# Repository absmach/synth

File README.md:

<div align="center">

### Design circuit boards as code.

Turn text-based circuit designs into KiCad schematics, PCB layouts, and bills of materials.

[Install](#install) · [Quick Start](#quick-start) · [Features](#features) · [Examples](#examples) · [Documentation](https://absmach.eu/docs/synth/user-guide/quick-start/) · [Contributing](#contributing)

</div>

## Introduction

Synth is an open-source compiler for electronic circuit boards. Describe components, connections, and board constraints in **SynthSpec**, a text-based design language; Synth checks the design and generates KiCad schematics, PCB layouts, and a bill of materials. Your `.synth` files hold the design intent, so you can edit them in your usual editor and review changes in Git. Engineers drive it from the command line, and AI agents drive the same compiler through its **Model Context Protocol (MCP)** server.

```synth
board "env_logger" {
    layers 2
    manufacturer "jlcpcb"

    group "USB-C INPUT / 3V3 LDO" color "#c2410c" {
      component J1: connector "usb_c_receptacle"
      component U1: regulator "ams1117_3v3" value "AMS1117-3.3"
      component C2: capacitor "c_generic_0805" value "22uF"
    }

    connect J1.vbus -> U1.vin
    connect J1.gnd  -> U1.gnd
    connect U1.vin  -> C2.p1
}
```

_An excerpt from the [environmental logger](examples/env_logger/env_logger.synth); the full design adds the MCU, sensor, CC pull-downs, and decoupling that the checks require._

<div align="center">

_An agent designing a two-layer NE555 LED blinker through the MCP server: searching the registry, authoring a missing part, setting placement overrides, and validating the board._

</div>

## Install

### Prebuilt binary

Every [release](https://github.com/absmach/synth/releases) ships a `synth` binary for five platforms, each with a SHA-256 checksum beside it.

| Platform       | Asset                     |
| -------------- | ------------------------- |
| Linux x86-64   | `synth-linux-amd64`       |
| Linux arm64    | `synth-linux-arm64`       |
| macOS arm64    | `synth-darwin-arm64`      |
| macOS x86-64   | `synth-darwin-amd64`      |
| Windows x86-64 | `synth-windows-amd64.exe` |

```bash
base="https://github.com/absmach/synth/releases/latest/download"
asset="synth-linux-amd64"          # pick your platform from the table above

curl -LO "$base/$asset"
curl -LO "$base/$asset.sha256"
sha256sum -c "$asset.sha256"       # macOS: shasum -a 256 -c "$asset.sha256"

sudo install -m 755 "$asset" /usr/local/bin/synth
synth --version
```

Verify the checksum before running the binary. On Windows, check it with `certutil -hashfile synth-windows-amd64.exe SHA256` and compare against the `.sha256` file.

The Linux binaries are built against glibc 2.35, so they run on Debian Bookworm, Ubuntu 22.04, and newer.

> [!NOTE]
> The component registry and example designs ship inside the repository and track `main`, which has moved ahead of the latest release. Pair a prebuilt binary with its own tag (`git checkout v0.1.1`, where the example paths differ from those below), or install from source to follow the Quick Start as written.

### Cargo

Synth is not on crates.io, so install it from Git. Requires Rust 1.100 or newer.

```bash
# Latest release
cargo install --git https://github.com/absmach/synth --tag v0.1.1 --locked synth-cli

# Current main
cargo install --git https://github.com/absmach/synth --locked synth-cli
```

> [!WARNING]
> Do not run `cargo install synth-cli`. The `synth-cli` crate on crates.io is an unrelated project — a WebAssembly-to-ARM compiler — not this one.

### From source

```bash
git clone https://github.com/absmach/synth.git
cd synth
cargo build -p synth-cli --release
./target/release/synth --help
```

The repository pins its toolchain in `rust-toolchain.toml`, so rustup fetches the right version automatically.

## Quick Start

Validate the minimal example and export a KiCad project. The example designs come from a checkout, so clone the repository (or `cd` into it) first:

```bash
synth validate fixtures/designs/hello.synth
synth export-kicad fixtures/designs/hello.synth --out output/hello
```

The minimal example declares an empty two-layer board. Use the [example designs](#examples) to explore circuits with components and connections.

For machine-readable diagnostics:

```bash
synth validate examples/env_logger/env_logger.synth --format json
```

Open exported projects in KiCad. Optional Gerber, drill, and STEP exports require `kicad-cli`; see the [KiCad workflow guide](docs/kicad-workflows.md) for export and review details.

For CI and release gates, `synth check DESIGN.synth --json` is the deterministic gate for validation, DRC and the testbench when one exists. A check that could not run is reported as `unknown` and blocks just as a failure does — see [release checks](docs/release-checks.md).

### Logging

Progress, retries, and degraded-check notices go to stderr as structured log events; stdout carries only the command's own output (JSON, reports, listings), so a pipeline can parse it without stripping prefixes. The default level is info. `-v` raises it to debug, `-vv` to trace, and `-q` shows errors only. `SYNTH_LOG` overrides both when one stage needs more detail:

```bash
synth -v export-kicad board.synth --out output/board
SYNTH_LOG=synth_router=debug,synth=info synth route board.synth
```

### Agent Integration

Start the MCP server over standard input and output:

```bash
synth mcp --stdio
```

Agents can retrieve the SynthSpec language reference, search the registry, validate designs, apply fixes, and invoke compiler stages. See the [MCP guide](crates/synth-mcp/README.md) for transports and tool details. For electrical checks, the [SPICE simulation skill](skills/spice-sim/SKILL.md) covers authoring a testbench, reading `synth sim` results, and reporting coverage.

## How It Works

```mermaid
flowchart LR
    source["SynthSpec source"] --> compiler["Parse & resolve"]
    compiler --> checks["Validate"]
    checks --> layout["Place & route"]
    layout --> export["KiCad project & BOM"]
    checks --> feedback["Diagnostics & fixes"]
    feedback --> source
```

Synth resolves parts from a component registry and lowers the source into a typed board representation. Compiler stages use that shared representation for electrical checks, layout, routing, and export. A local browser viewer displays the schematic and diagnostics as you edit.

## Features

| Area               | Capabilities                                                                                                                                    |
| ------------------ | ----------------------------------------------------------------------------------------------------------------------------------------------- |
| Design language    | SynthSpec parser, typed board IR, components, connections, differential pairs, keepouts, and placement hints                                    |
| Validation         | Electrical-rule checks, design-rule checks, structured diagnostics with source locations and suggested fixes, and SMT-backed quantitative fixes |
| Layout and routing | Deterministic schematic layout, component placement, and multilayer routing, so generated artifacts are reproducible                            |
| KiCad integration  | Project, schematic, PCB, and BOM export; optional fabrication outputs through `kicad-cli`                                                       |
| Component registry | Versioned parts, project and user overlays, search, import, and authoring tools                                                                 |
| Developer tools    | CLI, JSON diagnostics, and an MCP server exposing validation, registry search, placement, routing, and export                                   |

## Examples

| Design                                                                                             | What it demonstrates                                                          |
| -------------------------------------------------------------------------------------------------- | ----------------------------------------------------------------------------- |
| [Hello](fixtures/designs/hello.synth)                                                              | The smallest board declaration                                                |
| [Resistor divider](examples/divider/divider.synth)                                                 | A DC operating-point simulation with `synth sim`                              |
| [RC filter](examples/rc_filter/rc_filter.synth)                                                    | An AC sweep measuring the -3 dB corner with `synth sim`                       |
| [LED current](examples/led/led.synth)                                                              | A branch-current measure checked against a limit with `synth sim`             |
| [Environmental logger](examples/env_logger/env_logger.synth)                                       | USB-C power, a regulator, an MCU, an environmental sensor, and a debug header |
| [Sensor logger](examples/sensor_logger/sensor_logger.synth)                                        | A larger design with dual I²C sensors, SPI flash, and status LEDs             |
| [Placement and differential pairs](examples/placement_and_diff_pair/placement_and_diff_pair.synth) | Placement hints, differential-pair constraints, and keepout regions           |
| [RP2350 development board](examples/rp2350/)                                                       | Clean-netlist FreeRouting, zone refill, and compact outlines                  |

Additional language and validation cases live in [fixtures](fixtures/designs/README.md). Part definitions live in the [component registry](registry/README.md).

_Pre-generated compact RP2350 routed review artifact; open the [KiCad board](examples/rp2350/rp2350_devboard_freerouting_clean.kicad_pcb)
for an interactive review._

## Documentation

- [Release checks](docs/release-checks.md) — the `synth check` gate, tri-state native stages, and export overrides.
- [KiCad workflows](docs/kicad-workflows.md) — exported projects, validation, BOMs, and fabrication outputs.
- [SPICE simulation](docs/spice-sim.md) — `synth sim` testbenches, analyses, measures and ngspice setup.
- [Schematic procedures](docs/schematic-procedures.md) — schematic generation and review.
- [Diagnostic reference](docs/diagnostics/README.md) — diagnostic codes and repair guidance.
- [Diagnostic protocol](docs/protocol-v1.0.md) — the machine-readable diagnostic format.
- [Component registry](registry/README.md) — part definitions and registry structure.
- [MCP server](crates/synth-mcp/README.md) — agent tools and integration.
- [Glossary](GLOSSARY.md) — shared vocabulary for simulation and check stages.

## Contributing

Contributions to the compiler, component registry, examples, and documentation are welcome. Use [issues](https://github.com/absmach/synth/issues) to report bugs or discuss a change, and submit a pull request with a focused description and relevant validation.

Before submitting code, run the workspace checks:

```bash
make verify
```

This checks formatting, compilation, Clippy lints, the workspace tests, and registry tests. Run `make help` to see individual development commands.

## License

Synth is licensed under the [Apache License 2.0](LICENSE).

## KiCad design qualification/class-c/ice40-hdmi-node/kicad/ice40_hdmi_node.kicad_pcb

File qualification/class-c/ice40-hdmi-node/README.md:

# iCE40HX4K HDMI (DVI-style TMDS) node (Class C, case 3)

An iCE40HX4K FPGA in a 144-pin TQFP (0.5 mm pitch) drives an HDMI Type-A receptacle through four TMDS-style pairs with 270 ohm source resistors. The board also has level-shifted DDC lines, a hot-plug-detect divider, a fused +5 V HDMI pin, an SPI boot flash and four status LEDs. It is powered from a 5 V terminal and is 88.2 x 79.0 mm on six copper layers.

This is the Class C case 3 attempt for #330 under #40. The board declares impedance, pair spacing and skew for its TMDS pairs, and the delivered copper is measured against those declarations. Only the skew budget is met; spacing, coupling and impedance are not (see [#447](https://github.com/absmach/synth/issues/447), open). The interface is DVI-style and no HDMI compliance is claimed.

The prompt to reproduce the board is in [`PROMPT.md`](PROMPT.md), written from the finished board. The prompts the agent ran are in the history at `45b6f93d`.

## The board

### Parts

| Group         | Parts                                                                                                                                         |
| ------------- | --------------------------------------------------------------------------------------------------------------------------------------------- |
| Power entry   | `J1` JST B2B-XH-A 2-pin header, 5.0 to 5.25 V in                                                                                              |
| Power entry   | `F1` Bourns MF-MSMF110/16-2 PTC fuse: 1.1 A hold, 2.2 A trip, 16 V                                                                            |
| Power entry   | `D1` Nexperia PTVS6V0S1UR TVS: 6.0 V standoff, 6.67 V minimum breakdown                                                                       |
| Power entry   | `Q3` Vishay SI2301CDS P-MOSFET (20 V) as the reverse-polarity stage; gate to GND through `R40` (10 k); 5.1 V zener `D_GZ` from gate to source |
| Power entry   | `C1`, test point `TP1`                                                                                                                        |
| 3.3 V         | `U1` Diodes AP7361C-33E-13 LDO: 1 A, SOT-223, stable with ceramic capacitors                                                                  |
| 3.3 V         | `C2` to `C5` 10 uF                                                                                                                            |
| 3.3 V         | `R_SURGE` 1 ohm series resistor in front of `U1`; it keeps a `D1` clamp event off the regulator input                                         |
| 1.2 V core    | `U2` Texas Instruments TLV70012DDCR, TSOT-23-5, with `C6` and `C7`                                                                            |
| 1.2 V core    | PLL supplies `VCCPLL0` and `VCCPLL1` fed through ferrite beads `L1` and `L2`, with `C21` and `C22`                                            |
| FPGA          | `U3` Lattice iCE40HX4K-TQ144, 107 user I/O                                                                                                    |
| FPGA          | 100 nF decoupling `C10` to `C20`, `C24`, `C25` to `C27`                                                                                       |
| FPGA          | `X1` SiTime SiT8008 25 MHz oscillator with `C23`                                                                                              |
| Configuration | `U4` Winbond W25Q128JVSIQ, SOIC-8 208 mil, master SPI                                                                                         |
| Configuration | `R30` and `R31` pull up `CDONE` and `CRESET_B`; `R32` and `R33` pull up the flash write-protect and hold pins                                 |
| HDMI          | `J2` Amphenol 10029449-111RLF HDMI Type-A receptacle                                                                                          |
| HDMI          | `R1` to `R8` 270 ohm TMDS source resistors, in one column between the FPGA and the connector                                                  |
| HDMI          | `D3` onsemi SRV05-4 4-line ESD array on the DDC and HPD lines                                                                                 |
| HDMI          | `D8` and `D9` TI TPD4E05U06 4-channel ESD arrays (0.5 pF per channel) on the eight TMDS lines                                                 |
| HDMI          | `F2` Bourns MF-NSMF050-2 PTC fuse (0.5 A hold) on the +5 V pin                                                                                |
| HDMI          | DDC level shifters `Q1` and `Q2` (IRLML6244), `R9` and `R10` (2 k to +5 V), `R11` and `R12` (10 k to 3.3 V)                                   |
| HDMI          | HPD divider `R13` (10 k) and `R14` (20 k)                                                                                                     |
| Indicators    | `D4` and `D5` green, `D6` and `D7` red LEDs with 470 ohm resistors `R20` to `R23`                                                             |
| Indicators    | `D5` is driven through N-FET `Q4` (AO3400A, gate on `CDONE`), so the open-drain `CDONE` net sees only a gate                                  |
| Test points   | `TP1` to `TP7` on the bottom side: +5 V, +3.3 V, +1.2 V, GND, CDONE, CRESET_B, +5 V_HDMI                                                      |
| Mechanical    | Two M2.5 mounting holes, `H1` and `H2`                                                                                                        |

### Layout

| Item                    | Value                                                                                                                                          |
| ----------------------- | ---------------------------------------------------------------------------------------------------------------------------------------------- |
| Outline                 | 88.5 x 82.0 mm; 1.47 mm thick in the STEP model                                                                                                |
| Copper layers           | 6                                                                                                                                              |
| Stackup                 | JLCPCB `JLC06161H-3313`: prepreg 3313 0.0994 mm er 4.1, core 0.55 mm er 4.6, prepreg 2116 0.1088 mm er 4.16; outer copper 35 um, inner 15.2 um |
| Parts in the BOM        | 83 (74 parts plus 2 mounting holes and 7 test points, which are board features)                                                                |
| Parts placed in the CPL | 74                                                                                                                                             |
| Nets                    | 49                                                                                                                                             |
| Track segments          | 887                                                                                                                                            |
| Vias                    | 141, all at 0.46/0.2 mm                                                                                                                        |
| Track length            | 1922.6 mm                                                                                                                                      |
| Zones and planes        | GND zone on each of the six copper layers; two keepout areas on all layers for the mounting screw heads (no tracks, vias or pour)              |
| Fab package             | `fab/gerbers.zip`, `fab/bom.csv`, `fab/cpl.csv`                                                                                                |
| 3D models               | `models/` holds the STEP body of every part the board references and the board model `ice40_hdmi_node.step`. The board file reaches them by the relative path `${KIPRJMOD}/../models/`. Mounting holes and fiducials have no body. A part that KiCad's library has no model for is a simplified box of its envelope. |
| Schematic               | `images/schematic.pdf`: one vector page, because the board fits one sheet, plotted by `kicad-cli sch export pdf`. |

### Checks

| Check                                  | Result                               | Notes                                                                                                                                       |
| -------------------------------------- | ------------------------------------ | ------------------------------------------------------------------------------------------------------------------------------------------- |
| KiCad DRC (10.0.8, --refill-zones)     | 0 errors, 0 unconnected, 0 warnings  | None                                                                                                                                        |
| KiCad ERC (10.0.8)                     | 0 errors, 0 unconnected, 25 warnings | 18 `lib_symbol_issues`, 5 `lib_symbol_mismatch`, 2 `pin_to_pin`; the 2 `pin_to_pin` are on `CBSEL0` and `CBSEL1`, tied to ground on purpose |
| Routing (KiCadRoutingTools `9399bfb2`) | 49 of 49 nets routed                 | Measured on the board file                                                                                                                  |
| Synth build                            | `main` `8f148bc0` plus 3 fixes        | Branches `feat/jlc-advanced-trace-width` (0.09 mm minimum track), #529 (mirrored text) and `fix/stub-net-by-name` (net spelling, island ties); none is merged, so a plain `main` build does not reproduce this export |
| Gerbers                                | Plotted from refilled zones          | Zones were refilled before the package was written                                                                                          |
| Synth DFM (not a gate)                 | 3 danger, 5 warning on copper        | Pad to via gaps of 0.070 mm at `D8.2` and `U3.24`, and 0.095 mm at `U3.4`; JLCPCB lists 0.0889 mm (3.5 mil) as its minimum on 4 and 6 layers, so the two 0.070 mm gaps are below it. Also 82 silkscreen-to-pad and 19 silkscreen-to-hole danger findings, which JLCPCB clips |
| Via in pad                             | Required                             | The source declares `requires via_in_pad`. An export without it leaves `+3V3` open at `U3` pin 131 and does not release (#512).             |

### Design figures

| Area             | Item                 | Value                                                                                                                                                    | Basis                                               |
| ---------------- | -------------------- | -------------------------------------------------------------------------------------------------------------------------------------------------------- | --------------------------------------------------- |
| FPGA             | User I/O             | 107 on the iCE40HX4K-TQ144                                                                                                                               | Lattice DS1040                                      |
| FPGA             | Part model           | `registry/parts/fpga/ice40hx4k_tq144.synth.toml` is built from KiCad's `FPGA_Lattice:ICE40HX4K-TQ144` symbol with the pin functions of DS1040            | Lattice DS1040                                      |
| Signal integrity | Lane pin assignment  | Four adjacent pin pairs on the FPGA's left side (1-2, 3-4, 7-8, 9-10), in the connector's lane order, so no pair crosses another                         | Measured on the board file                          |
| Signal integrity | Leg definition       | Each leg is the FPGA-to-resistor net plus the resistor-to-connector net; gaps are plan-view, centre to centre, regardless of layer                       | Measured on the board file                          |
| Signal integrity | `D0`                 | P 44.7 mm, N 34.3 mm, skew 10.46 mm, vias 5 / 6, gap min / median 0.17 / 1.80 mm                                                                         | Measured on the board file                          |
| Signal integrity | `D1`                 | P 45.3 mm, N 34.7 mm, skew 10.53 mm, vias 5 / 5, gap min / median 0.00 / 2.13 mm                                                                         | Measured on the board file                          |
| Signal integrity | `D2`                 | P 40.1 mm, N 31.8 mm, skew 8.28 mm, vias 4 / 6, gap min / median 0.00 / 1.71 mm                                                                          | Measured on the board file                          |
| Signal integrity | `CK`                 | P 39.5 mm, N 36.2 mm, skew 3.34 mm, vias 3 / 5, gap min / median 0.04 / 1.77 mm                                                                          | Measured on the board file                          |
| Signal integrity | Minimum gaps         | Gaps below the 0.127 mm track width mean the legs cross in plan view on different layers; they are not a copper spacing                                  | Measured on the board file                          |
| Signal integrity | Skew measure         | Sums of track segments; the DRC's own length-matching figures are not used                                                                               | Measured on the board file                          |
| Signal integrity | Skew budget          | 25 mm declared, met on all four lanes                                                                                                                    | Measured on the board file                          |
| Signal integrity | Skew limit           | 0.15 Tbit within a pair; at 25 MHz Tbit is 4.0 ns, so 0.6 ns, about 85 mm at 7.0 ps/mm; the 25 mm budget is 29 % of it                                   | TI SLVA747 (secondary source); calculated           |
| Signal integrity | Inter-pair mismatch  | Mean pair lengths differ by up to 4.06 mm; no inter-pair budget is declared                                                                              | Measured on the board file                          |
| Signal integrity | Impedance estimate   | 54.5 ohm single-ended, 96.7 ohm differential at 0.127 mm width and 0.15 mm gap, outer-layer microstrip only; it does not describe inner-layer runs       | Calculated (closed-form microstrip)                 |
| Signal integrity | Drive levels         | Each line is LVCMOS33 through 270 ohm into the sink's 50 ohm to 3.3 V: 2.78 V to 3.3 V, 0.52 V single-ended; FPGA pin output impedance not included      | Calculated                                          |
| Signal integrity | Edge rate            | 20 to 80 % edges of at least 0.728 ns at the fast corner; TMDS and source classes declare `edge_rate medium`, a 6 mm window for `W-SYNTH-DRC-016` (#445) | Lattice IBIS model `ice40.ibs` rev 2.5              |
| Signal integrity | Return-via distances | `D0` 0.63 to 4.64 mm, `D1` 1.00 to 4.08 mm, `D2` 0.67 to 5.59 mm, `CK` 0.63 to 4.01 mm; all are inside the 6 mm window                                   | Measured on the board file                          |
| Signal integrity | HPD divider          | 5 V x 20 / (10 + 20) = 3.33 V at the FPGA                                                                                                                | Calculated                                          |
| Power            | Input range          | `J1` takes 5.0 to 5.25 V; protection is sized for a 5.5 V maximum; a 4.75 V low-end check shows why 5.0 V is the minimum                                 | Calculated                                          |
| Power            | `D1` standoff        | 6.0 V standoff above the 5.5 V maximum input                                                                                                             | Nexperia PTVS6V0S1UR datasheet                      |
| Power            | HDMI pin 18 drop     | Worst case 0.065 V in `F1`, 0.034 V in `Q3`, 0.039 V in `F2`, 0.138 V in all                                                                             | Calculated                                          |
| Power            | HDMI pin 18 voltage  | A 5.00 V input gives 4.86 V against the 4.8 V minimum; pin 18 needs at least 4.94 V at `J1`                                                              | Calculated                                          |
| Power            | Regulator ratings    | `RthJA` 110 degC/W (SOT-223); 6.0 V recommended, 6.5 V absolute maximum input; 360 mV typical dropout at 1 A                                             | Diodes DS37274 Rev. 5-2                             |
| Power            | Dropout margin       | At the 4.40 V worst-case regulator input, `U1` has 1.10 V to spare against 0.36 V typical dropout at 1 A                                                 | Diodes DS37274 Rev. 5-2; calculated                 |
| Thermal          | 3.3 V load           | `U2` 200 mA, `U4` 25 mA, LEDs 28 mA: 253 mA                                                                                                              | TI SBVS173; Winbond W25Q128JV datasheet; calculated |
| Thermal          | `U1` junction        | 0.47 W in `U1`; Tj 77 degC at 25 degC and 122 degC at 70 degC ambient                                                                                    | Diodes DS37274 Rev. 5-2; calculated                 |
| Protection       | Surge clamp          | `D1` clamps at up to 10.3 V                                                                                                                              | Nexperia PTVS6V0S1UR datasheet                      |
| Protection       | Surge current        | `R_SURGE` limits the current into `C2` and `C3` (20 uF) to 5.8 A; a 60 ns event raises the regulator input by about 0.02 V                               | Calculated                                          |
| Protection       | `Q3` gate            | `D_GZ` holds the `Q3` gate-source voltage under 5.4 V against its 8 V rating                                                                             | Vishay SI2301CDS datasheet; calculated              |
| Assembly         | Via in pad           | The TQFP-144 escape does not need it; the plane stage does until #512 is fixed. A few vias sit in small-part and test-point pads                         | Measured on the board file                          |

### Sourcing

| Item                        | Status                 | Notes                                         |
| --------------------------- | ---------------------- | --------------------------------------------- |
| 74 placed parts             | sourced                | Distributor and order number in `fab/bom.csv` |
| `H1`, `H2`, `TP1` to `TP7`  | board feature, no part | Not placed                                    |
| JLCPCB DFM and BOM matching | not run                | No run is recorded for the package in `fab/`  |

## Not verified by Synth

| Area                   | What is not verified                                                                                                                                                               |
| ---------------------- | ---------------------------------------------------------------------------------------------------------------------------------------------------------------------------------- |
| HDMI compliance        | None is claimed. The interface is DVI-style, with LVCMOS33 outputs through series resistors, because the iCE40 cannot source TMDS levels.                                          |
| Coupled pairs          | The pairs are routed as independent nets on different layers, so they are not a coupled differential interface.                                                                    |
| Impedance              | The differential impedance is not established. Only an analytic estimate for an outer-layer microstrip is given.                                                                   |
| Pair spacing           | The median gap between the legs, 1.71 to 2.13 mm, is wider than the declared 0.15 mm coupling gap, so the legs are not coupled.                                                    |
| Sustained over-voltage | While `D1` holds the rail near 7.0 V until `F1` opens, the regulator input is about 6.75 V, 0.25 V over its 6.5 V rating.                                                          |
| `R_SURGE` pulse rating | The 5.8 A, 60 ns event is not checked against the resistor's pulse-load curve.                                                                                                     |
| Back-drive             | A powered sink back-powers the FPGA banks through the 270 ohm resistors when the board is off. No isolation switch is fitted. Do not connect a powered sink to an unpowered board. |
| FPGA I/O current       | The thermal budget leaves about 0.02 A for the FPGA's 3.3 V I/O at 70 degC ambient. That current depends on the FPGA design and is not counted.                                    |
| Test-point probing     | The effect of filled vias in the `TP2` and `TP5` pads on probing is not assessed.                                                                                                  |
| Fabrication checks     | No JLCPCB DFM or BOM-matching run is recorded for the package in `fab/`.                                                                                                           |
| Independent sign-off   | The independent PCB review required by #40 is still open.                                                                                                                          |

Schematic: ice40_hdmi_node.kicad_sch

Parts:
C1, C2, C3, C4, C5: 10uF; C_0805_2012Metric
C6, C7: 1uF; C_0603_1608Metric
C8: 100nF; C_0603_1608Metric
C10, C11, C12, C13, C14, C15, C16, C17, C18, C19, C20, C21, C22, C23, C24, C25, C26, C27: 100nF; C_0402_1005Metric
D1: PTVS6V0S1UR; Nexperia_CFP3_SOD-123W; MPN PTVS6V0S1UR
D3: SRV05-4MR6T1G; SOT-23-6; MPN SRV05-4MR6T1G
D4, D5: 0603-GREEN; LED_0603_1608Metric; MPN 0603-GREEN; LCSC C72043
D6, D7: 0603-RED; LED_0603_1608Metric; MPN 0603-RED; LCSC C2286
D8, D9: TPD4E05U06DQAR; USON-10_2.5x1.0mm_P0.5mm; MPN TPD4E05U06DQAR; LCSC C138714
D_GZ: 5V1; D_SOD-123; MPN BZT52C5V1-TP; LCSC C78728
F1: MF-MSMF110/16-2; Fuse_1812_4532Metric; MPN MF-MSMF110/16-2; LCSC C210834
F2: MF-NSMF050-2; Fuse_1206_3216Metric; MPN MF-NSMF050-2; LCSC C75464
H1, H2: (no value); MountingHole_2.5mm
J1: B2B-XH-A; JST_XH_B2B-XH-A_1x02_P2.50mm_Vertical; MPN B2B-XH-A
J2: 10029449-111RLF; HDMI_A_Amphenol_10029449-x01xLF_Horizontal; MPN 10029449-111RLF; LCSC C427307
L1, L2: (no value); L_0603_1608Metric
Q1, Q2: IRLML6244TRPBF; SOT-23; MPN IRLML6244TRPBF; LCSC C143946
Q3: SI2301CDS-T1-GE3; SOT-23; MPN SI2301CDS-T1-GE3; LCSC C10487
Q4: AO3400A; SOT-23; MPN AO3400A
R1, R2, R3, R4, R5, R6, R7, R8: 270; R_0603_1608Metric
R9, R10: 2k; R_0603_1608Metric
R11, R12, R13, R30, R31, R32, R33, R40: 10k; R_0603_1608Metric
R14: 20k; R_0603_1608Metric
R20, R21, R22, R23: 470; R_0603_1608Metric
R_SURGE: 1; R_1206_3216Metric
TP1: +5V; TestPoint_Pad_D1.5mm
TP2: +3V3; TestPoint_Pad_D1.5mm
TP3: +1V2; TestPoint_Pad_D1.5mm
TP4: GND; TestPoint_Pad_D1.5mm
TP5: CDONE; TestPoint_Pad_D1.5mm
TP6: CRESET_B; TestPoint_Pad_D1.5mm
TP7: +5V_HDMI; TestPoint_Pad_D1.5mm
U1: AP7361C-33E; SOT-223-3_TabPin2; MPN AP7361C-33E-13; LCSC C500795
U2: TLV70012DDCR; TSOT-23-5; MPN TLV70012DDCR; LCSC C69446
U3: ICE40HX4K-TQ144; TQFP-144_20x20mm_P0.5mm; MPN ICE40HX4K-TQ144; LCSC C1521989
U4: W25Q128JVSIQ; SOIC-8_5.3x5.3mm_P1.27mm; MPN W25Q128JVSIQ; LCSC C97521
X1: 25MHz; Oscillator_SMD_SiT_PQFN-4Pin_5.0x3.2mm

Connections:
+1V2: C7.1, C10.1, C11.1, C12.1, C13.1, L1.1, L2.1, TP3.1, U2.5 (OUT), U3.27 (VCC), U3.40 (VCC), U3.92 (VCC), U3.111 (VCC)
+1V2_PLL0: C21.1, L1.2, U3.54 (VCCPLL0)
+1V2_PLL1: C22.1, L2.2, U3.126 (VCCPLL1)
+3V3: C4.1, C5.1, C6.1, C14.1, C15.1, C16.1, C17.1, C18.1, C19.1, C20.1, C23.1, C24.1, C25.1, C26.1, C27.1, Q1.1 (G), Q2.1 (G), R11.1, R12.1, R20.1, R21.1, R30.1, R31.1, R32.1, R33.1, TP2.1, U1.3 (VO), U2.1 (IN), U2.3 (EN), U3.6 (VCCIO_3), U3.30 (VCCIO_3), U3.46 (VCCIO_2), U3.57 (VCCIO_2), U3.72 (VCC_SPI), U3.89 (VCCIO_1), U3.100 (VCCIO_1), U3.108 (VPP_2V5), U3.109 (VPP_FAST), U3.123 (VCCIO_0), U3.131 (VCCIO_0), U4.8 (VCC), X1.1 (OE), X1.4 (Vdd)
+5V: C1.1, D_GZ.1 (K), F2.1, Q3.2 (s), R_SURGE.1, TP1.1
+5V_HDMI: C8.1, D3.5 (VP), F2.2, J2.18 (+5V), R9.1, R10.1, TP7.1
+5V_IN: F1.1, J1.1
+5V_REG: C2.1, C3.1, R_SURGE.2, U1.1 (VI)
CDONE: Q4.1 (G), R30.2, TP5.1, U3.65 (CDONE)
CK_N_SRC: R8.1, U3.1 (IOL_2A)
CK_P_SRC: R7.1, U3.2 (IOL_2B)
CLK25: U3.128 (IOT_197_GBIN1), X1.3 (OUT)
CRESET_B: R31.2, TP6.1, U3.66 (~CRESET)
D0_N_SRC: R2.1, U3.3 (IOL_3A)
D0_P_SRC: R1.1, U3.4 (IOL_3B)
D1_N_SRC: R4.1, U3.7 (IOL_4A)
D1_P_SRC: R3.1, U3.8 (IOL_4B)
D2_N_SRC: R6.1, U3.9 (IOL_5A)
D2_P_SRC: R5.1, U3.10 (IOL_5B)
FLASH_HOLD: R33.2, U4.7 (~HOLD/~RESET/IO_{3})
FLASH_WP: R32.2, U4.3 (~WP/IO_{2})
GND: C1.2, C2.2, C3.2, C4.2, C5.2, C6.2, C7.2, C8.2, C10.2, C11.2, C12.2, C13.2, C14.2, C15.2, C16.2, C17.2, C18.2, C19.2, C20.2, C21.2, C22.2, C23.2, C24.2, C25.2, C26.2, C27.2, D1.2 (A), D3.2 (VN), D4.1 (K), D6.1 (K), D7.1 (K), D8.3 (GND), D8.8 (GND), D9.3 (GND), D9.8 (GND), J1.2, J2.2 (D2S), J2.5 (D1S), J2.8 (D0S), J2.11 (CKS), J2.17 (GND), J2.SH, Q4.2 (S), R14.2, TP4.1, U1.2 (GND), U2.2 (GND), U3.5 (GND), U3.13 (GND), U3.14 (GND), U3.53 (GNDPLL0), U3.59 (GND), U3.63 (IOB_103_CBSEL0), U3.64 (IOB_104_CBSEL1), U3.69 (GND), U3.86 (GND), U3.103 (GND), U3.127 (GNDPLL1), U3.132 (GND), U3.140 (GND), U4.4 (GND), X1.2 (GND)
HDMI_CK_N: D9.5 (D2-), J2.12 (CK-), R8.2
HDMI_CK_P: D9.4 (D2+), J2.10 (CK+), R7.2
HDMI_D0_N: D8.2 (D1-), J2.9 (D0-), R2.2
HDMI_D0_P: D8.1 (D1+), J2.7 (D0+), R1.2
HDMI_D1_N: D8.5 (D2-), J2.6 (D1-), R4.2
HDMI_D1_P: D8.4 (D2+), J2.4 (D1+), R3.2
HDMI_D2_N: D9.2 (D1-), J2.3 (D2-), R6.2
HDMI_D2_P: D9.1 (D1+), J2.1 (D2+), R5.2
HDMI_HPD: D3.4 (IO3), J2.19 (HPD/HEAC-), R13.1
HDMI_SCL: D3.3 (IO2), J2.15 (SCL), Q2.3 (D), R10.2
HDMI_SDA: D3.1 (IO1), J2.16 (SDA), Q1.3 (D), R9.2
HPD_FPGA: R13.2, R14.1, U3.19 (IOL_13A)
LED1_A: D6.2 (A), R22.2
LED2_A: D7.2 (A), R23.2
LED_DONE: D5.2 (A), R21.2
LED_DONE_K: D5.1 (K), Q4.3 (D)
LED_PWR: D4.2 (A), R20.2
LED_USER1: R22.1, U3.37 (IOB_56)
LED_USER2: R23.1, U3.39 (IOB_61)
Q3_GATE: D_GZ.2 (A), Q3.1 (g), R40.1
SCL_FPGA: Q2.2 (S), R12.2, U3.24 (IOL_17B)
SDA_FPGA: Q1.2 (S), R11.2, U3.23 (IOL_17A)
SPI_MISO: U3.68 (IOB_106_SDI), U4.2 (DO/IO_{1})
SPI_MOSI: U3.67 (IOB_105_SDO), U4.5 (DI/IO_{0})
SPI_SCK: U3.70 (IOB_107_SCK), U4.6 (CLK)
SPI_SS: U3.71 (IOB_108_SS), U4.1 (~CS)
VIN_FUSED: D1.1 (K), F1.2, Q3.3 (d)

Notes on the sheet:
POWER ENTRY
RAILS
FPGA
CONFIG FLASH
HDMI
STATUS
5 V in; PTC 1.1 A hold; TVS 6.0 V standoff above the 5.5 V maximum input; Q3 P-MOSFET reverse-polarity stage, gate to GND through R40.
TMDS drive: FPGA LVCMOS33 output + 270 ohm into 50 ohm sink pull-up to 3.3 V.
D8 and D9 are TPD4E05U06 ESD arrays (0.5 pF per channel) on the eight TMDS lines at the connector.

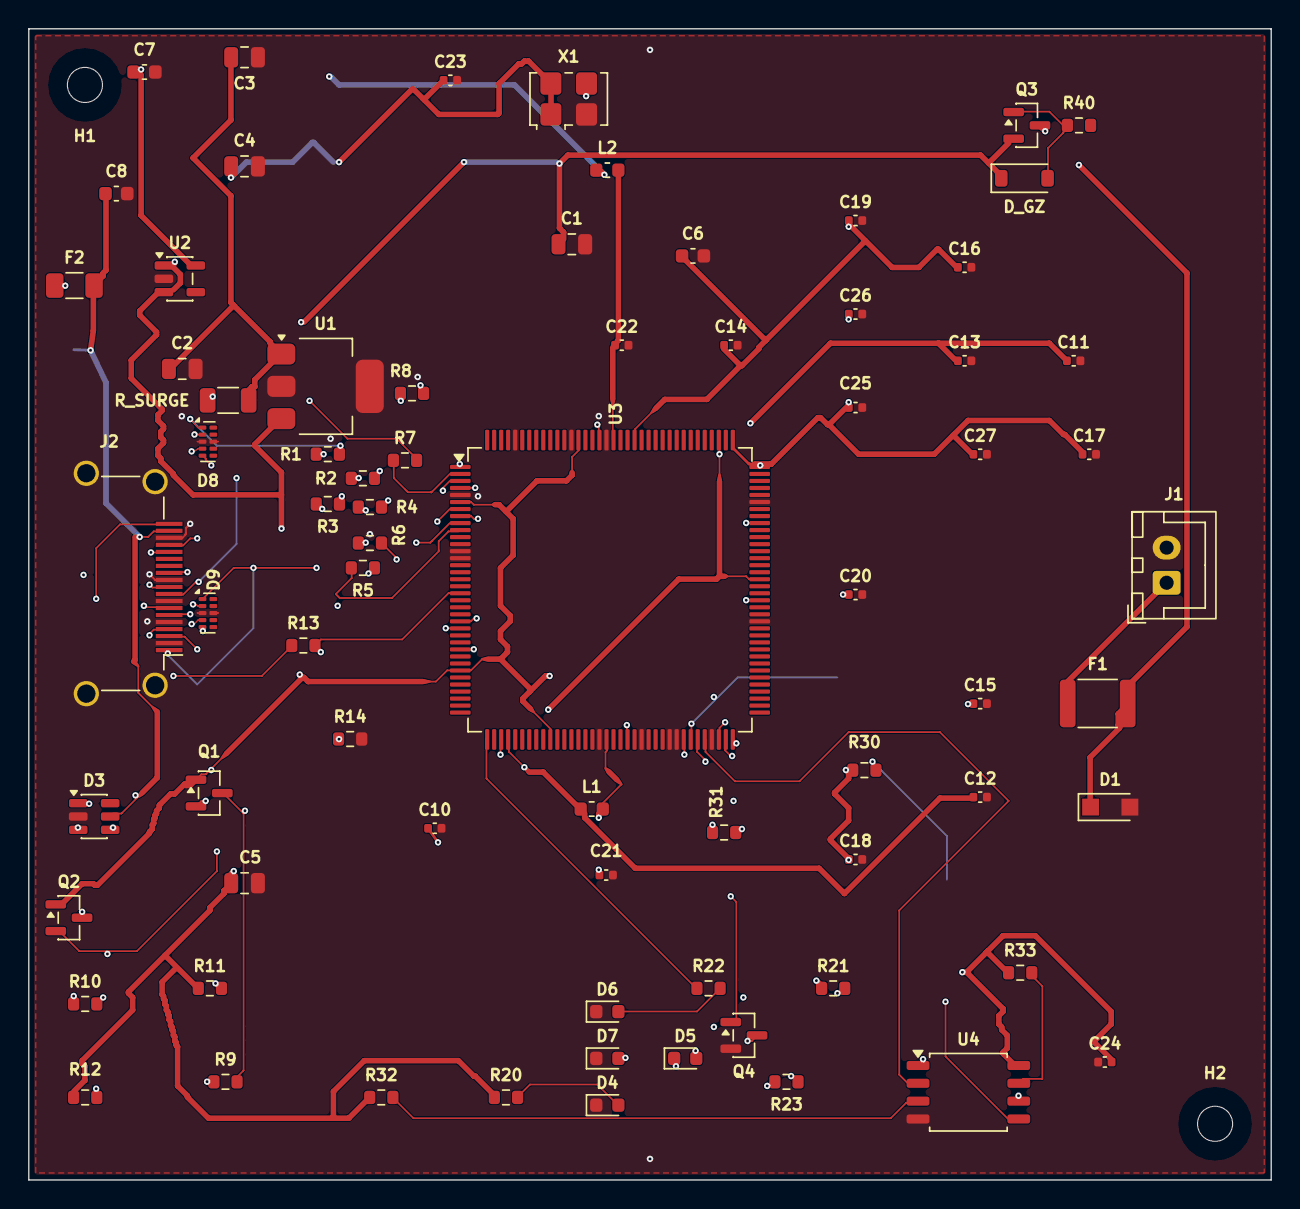
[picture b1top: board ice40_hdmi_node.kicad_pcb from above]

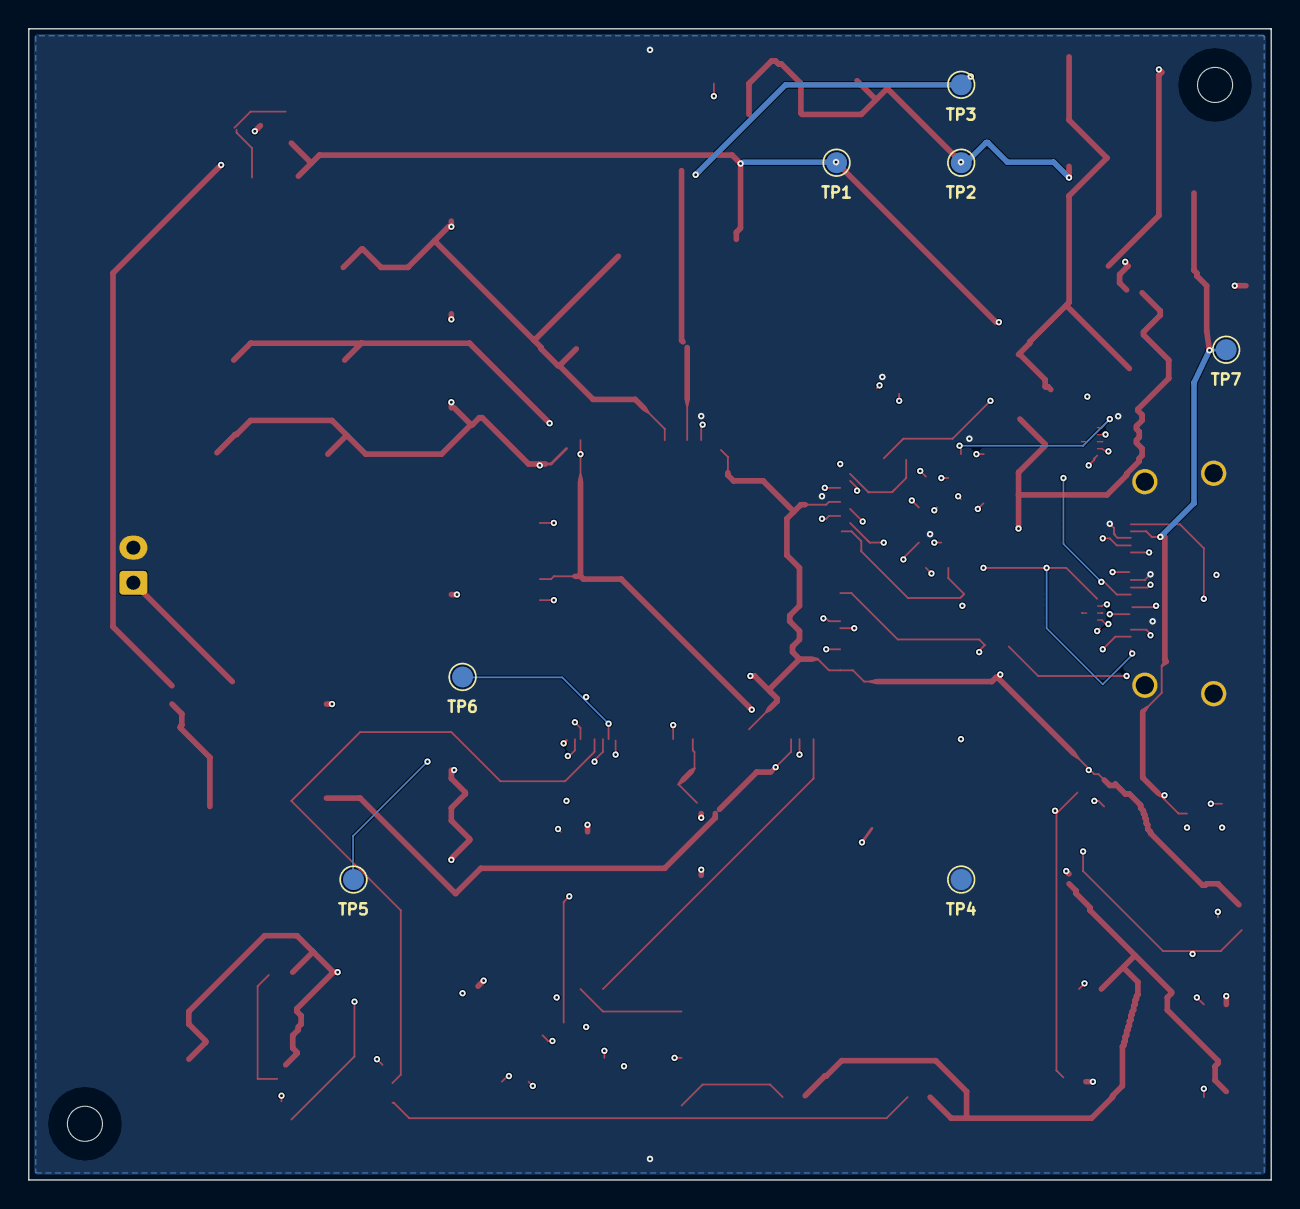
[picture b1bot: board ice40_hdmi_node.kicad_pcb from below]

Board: 6 copper layers, 88.5 x 82.0 mm, 83 parts (7 on the bottom side), 49 nets.

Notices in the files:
README.md:
License: Apache-2.0
